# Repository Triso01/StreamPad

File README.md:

The Case:

On the left the topplate and on the right the case.
You should print the TopPlate with 100% Gyroid infill.
The Case should be printed with 20%< Gyriod Infill.

The PCB:

The settings for the PCB should look like this: (You can change the color or surface finish!)

What is it made for?
I am a little streamer who needs a soundboard/"Streamdeck" and it is a good oportunity to get one "for free" :). 
I hope you all like the design (Its my first one in Fusion).

BOM:
HackPad Kit (You dont have a kit? You can find the components here: https://hackpad.hackclub.com/parts)
You also need 2x CD4051BM (these are Multiplexers)
!!The Case might change after I get the PCB!!

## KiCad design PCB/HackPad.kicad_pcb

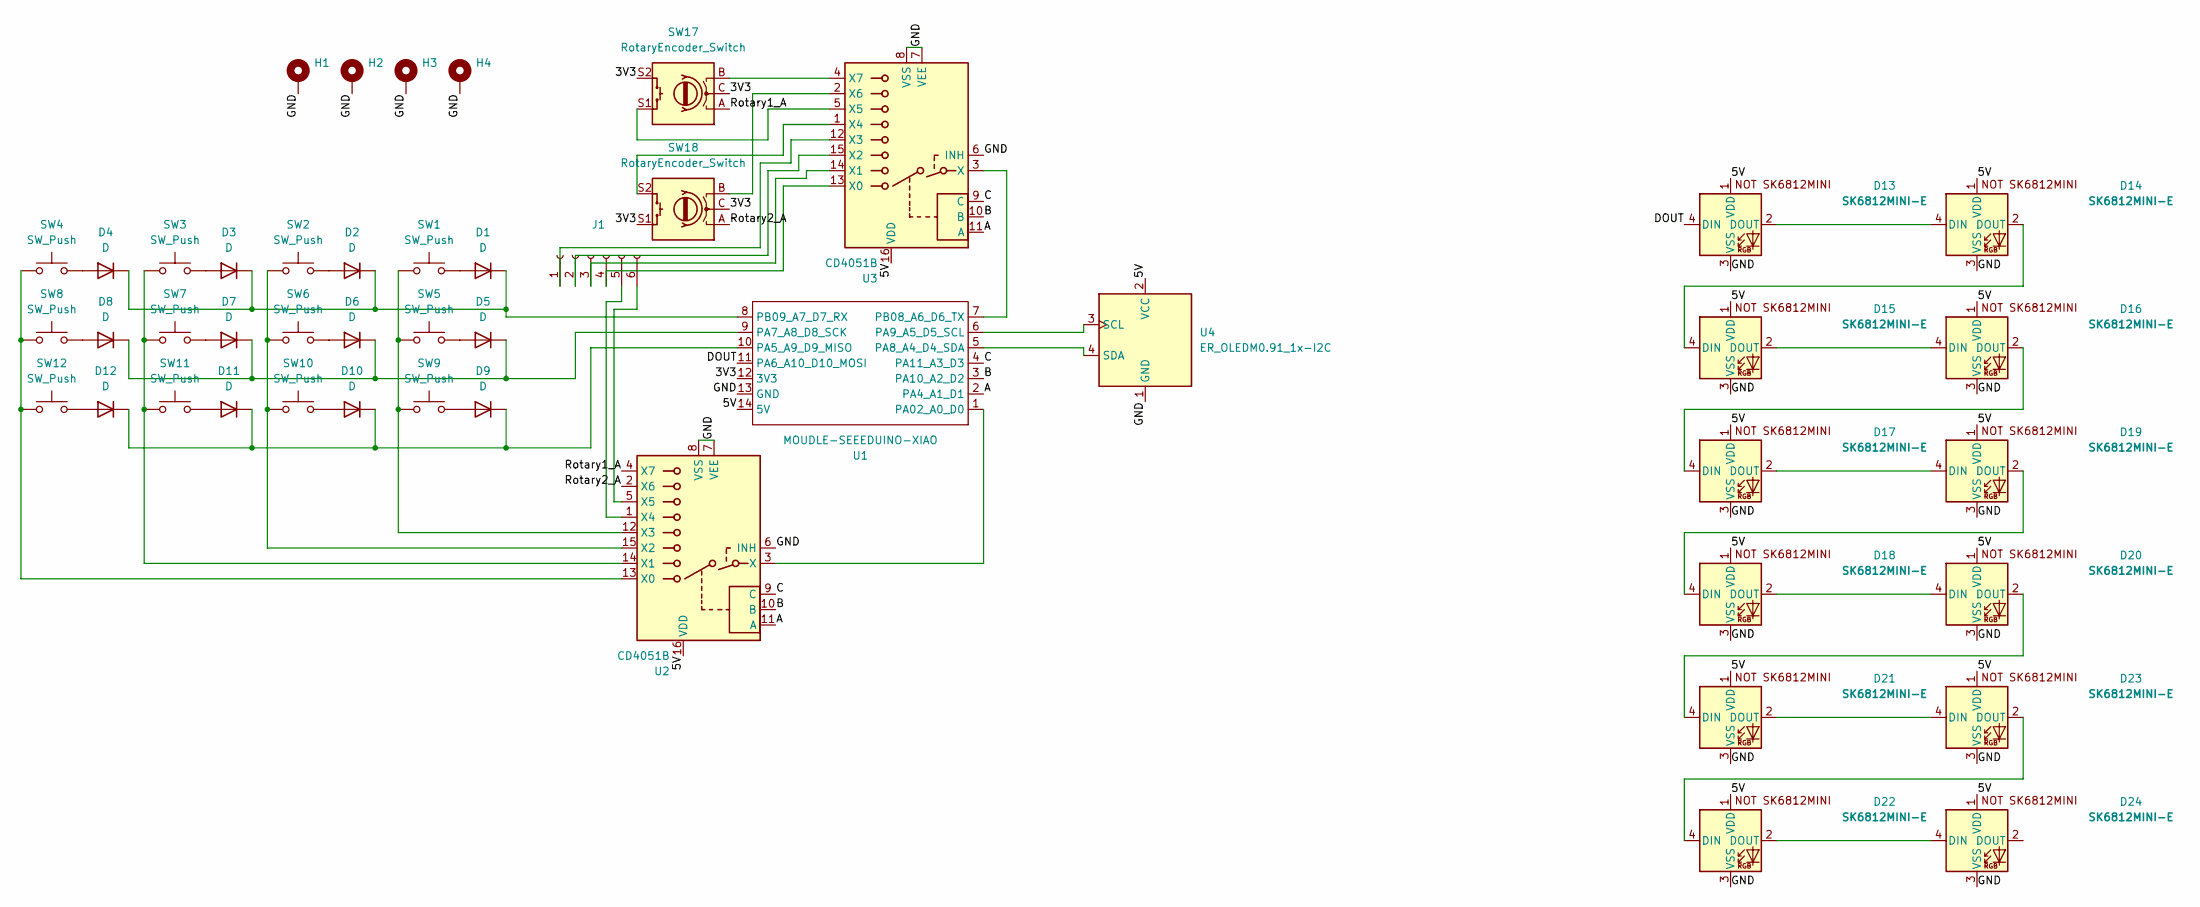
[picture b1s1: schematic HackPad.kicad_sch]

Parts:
D1, D2, D3, D4, D5, D6, D7, D8, D9, D10, D11, D12: D; D_DO-35_SOD27_P7.62mm_Horizontal
D13, D14, D15, D16, D17, D18, D19, D20, D21, D22, D23, D24: SK6812MINI-E; SK6812MINI-E_fixed
H1, H2, H3, H4: MountingHole_Pad; MountingHole_3.2mm_M3_DIN965_Pad
J1: Conn_01x06_Socket; PinSocket_1x06_P2.54mm_Vertical
SW1, SW2, SW3, SW4, SW5, SW6, SW7, SW8, SW9, SW10, SW11, SW12: SW_Push; SW_Cherry_MX_1.00u_PCB
SW17, SW18: RotaryEncoder_Switch; RotaryEncoder_Alps_EC11E-Switch_Vertical_H20mm_CircularMoun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
U1: MOUDLE-SEEEDUINO-XIAO; XIAO-Generic-Hybrid-14P-2.54-21X17.8MM
U2, U3: CD4051B; SOIC-16_3.9x9.9mm_P1.27mm
U4: ER_OLEDM0.91_1x-I2C

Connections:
/3V3: SW17.C, SW17.S2, SW18.C, SW18.S1, U1.12 (3V3)
/5V: D13.1 (VDD), D14.1 (VDD), D15.1 (VDD), D16.1 (VDD), D17.1 (VDD), D18.1 (VDD), D19.1 (VDD), D20.1 (VDD), D21.1 (VDD), D22.1 (VDD), D23.1 (VDD), D24.1 (VDD), U1.14 (5V), U2.16 (VDD), U3.16 (VDD), U4.2 (VCC)
/A: U1.2 (PA4_A1_D1), U2.11 (A), U3.11 (A)
/B: U1.3 (PA10_A2_D2), U2.10 (B), U3.10 (B)
/C: U1.4 (PA11_A3_D3), U2.9 (C), U3.9 (C)
/DOUT: D13.4 (DIN), U1.11 (PA6_A10_D10_MOSI)
/GND: D13.3 (VSS), D14.3 (VSS), D15.3 (VSS), D16.3 (VSS), D17.3 (VSS), D18.3 (VSS), D19.3 (VSS), D20.3 (VSS), D21.3 (VSS), D22.3 (VSS), D23.3 (VSS), D24.3 (VSS), H1.1 (1_1), H2.1 (1_1), H3.1 (1_1), H4.1 (1_1), U1.13 (GND), U2.6 (INH), U2.7 (VEE), U2.8 (VSS), U3.6 (INH), U3.7 (VEE), U3.8 (VSS), U4.1 (GND)
/Rotary1_A: SW17.A, U2.4 (X7)
/Rotary2_A: SW18.A, U2.2 (X6)
unnamed: D1.2 (A), SW1.1
unnamed: D1.1 (K), D2.1 (K), D3.1 (K), D4.1 (K), U1.8 (PB09_A7_D7_RX)
unnamed: D2.2 (A), SW2.1
unnamed: D3.2 (A), SW3.1
unnamed: D4.2 (A), SW4.1
unnamed: D5.2 (A), SW5.1
unnamed: D5.1 (K), D6.1 (K), D7.1 (K), D8.1 (K), U1.9 (PA7_A8_D8_SCK)
unnamed: D6.2 (A), SW6.1
unnamed: D7.2 (A), SW7.1
unnamed: D8.2 (A), SW8.1
unnamed: D9.2 (A), SW9.1
unnamed: D10.2 (A), SW10.1
unnamed: D9.1 (K), D10.1 (K), D11.1 (K), D12.1 (K), U1.10 (PA5_A9_D9_MISO)
unnamed: D11.2 (A), SW11.1
unnamed: D12.2 (A), SW12.1
unnamed: D13.2 (DOUT), D14.4 (DIN)
unnamed: D14.2 (DOUT), D15.4 (DIN)
unnamed: D15.2 (DOUT), D16.4 (DIN)
unnamed: D16.2 (DOUT), D17.4 (DIN)
unnamed: D17.2 (DOUT), D19.4 (DIN)
unnamed: D18.4 (DIN), D19.2 (DOUT)
unnamed: D18.2 (DOUT), D20.4 (DIN)
unnamed: D20.2 (DOUT), D21.4 (DIN)
unnamed: D21.2 (DOUT), D23.4 (DIN)
unnamed: D22.4 (DIN), D23.2 (DOUT)
unnamed: D22.2 (DOUT), D24.4 (DIN)
unnamed: J1.1, U3.12 (X3)
unnamed: J1.2, U3.15 (X2)
unnamed: J1.3, U3.14 (X1)
unnamed: J1.4, U3.13 (X0)
unnamed: J1.5, U2.1 (X4)
unnamed: J1.6, U2.5 (X5)
unnamed: U1.1 (PA02_A0_D0), U2.3 (X)
unnamed: U1.5 (PA8_A4_D4_SDA), U4.4 (SDA)
unnamed: U1.6 (PA9_A5_D5_SCL), U4.3 (SCL)
unnamed: U1.7 (PB08_A6_D6_TX), U3.3 (X)
unnamed: SW4.2, SW8.2, SW12.2, U2.13 (X0)
unnamed: SW3.2, SW7.2, SW11.2, U2.14 (X1)
unnamed: SW2.2, SW6.2, SW10.2, U2.15 (X2)
unnamed: SW1.2, SW5.2, SW9.2, U2.12 (X3)
unnamed: SW18.S2, U3.1 (X4)
unnamed: SW17.S1, U3.5 (X5)
unnamed: SW18.B, U3.2 (X6)
unnamed: SW17.B, U3.4 (X7)

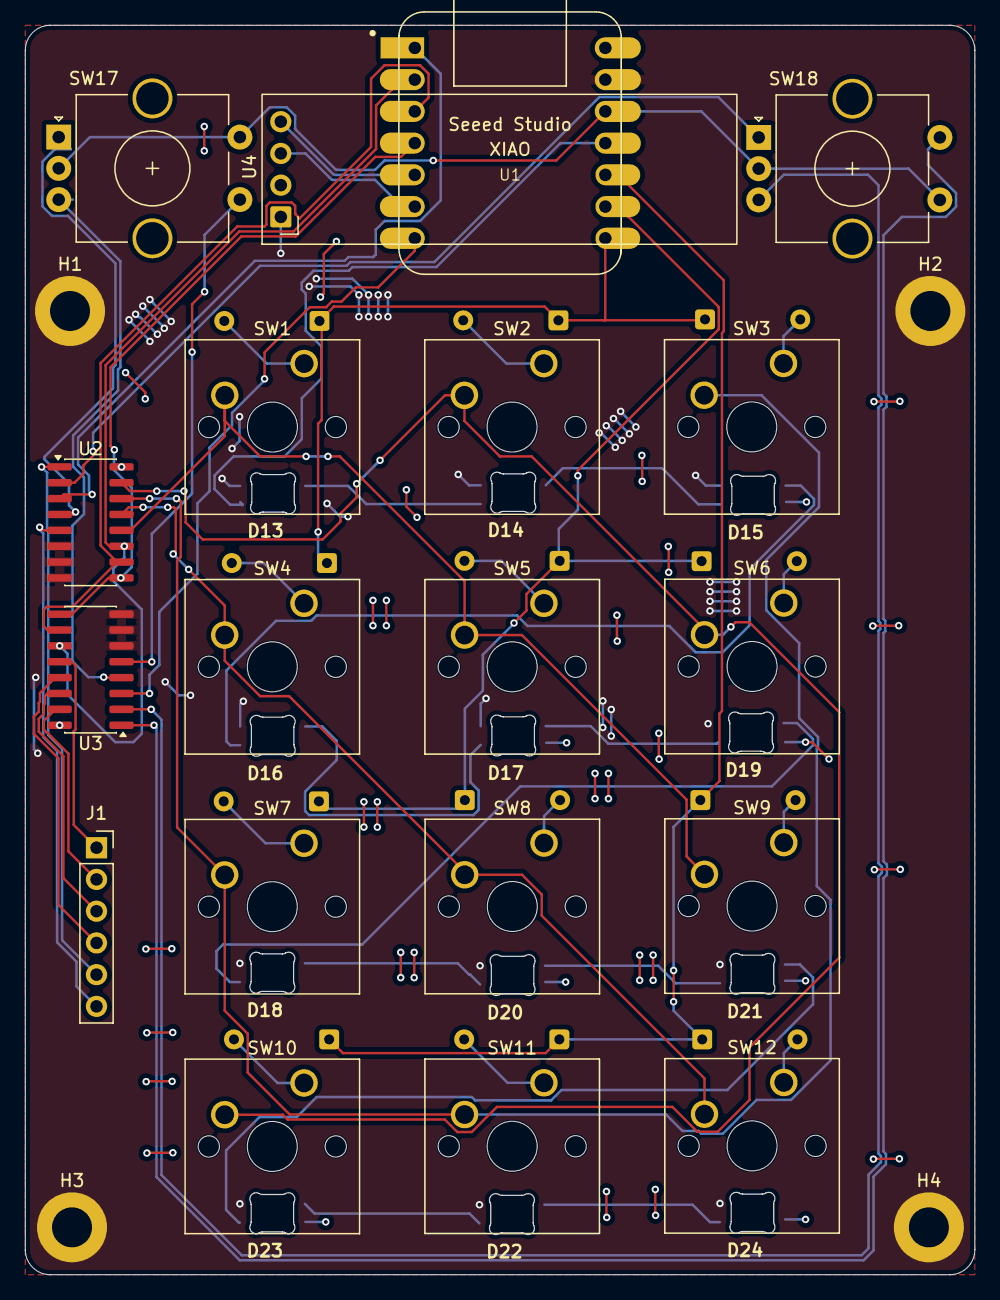
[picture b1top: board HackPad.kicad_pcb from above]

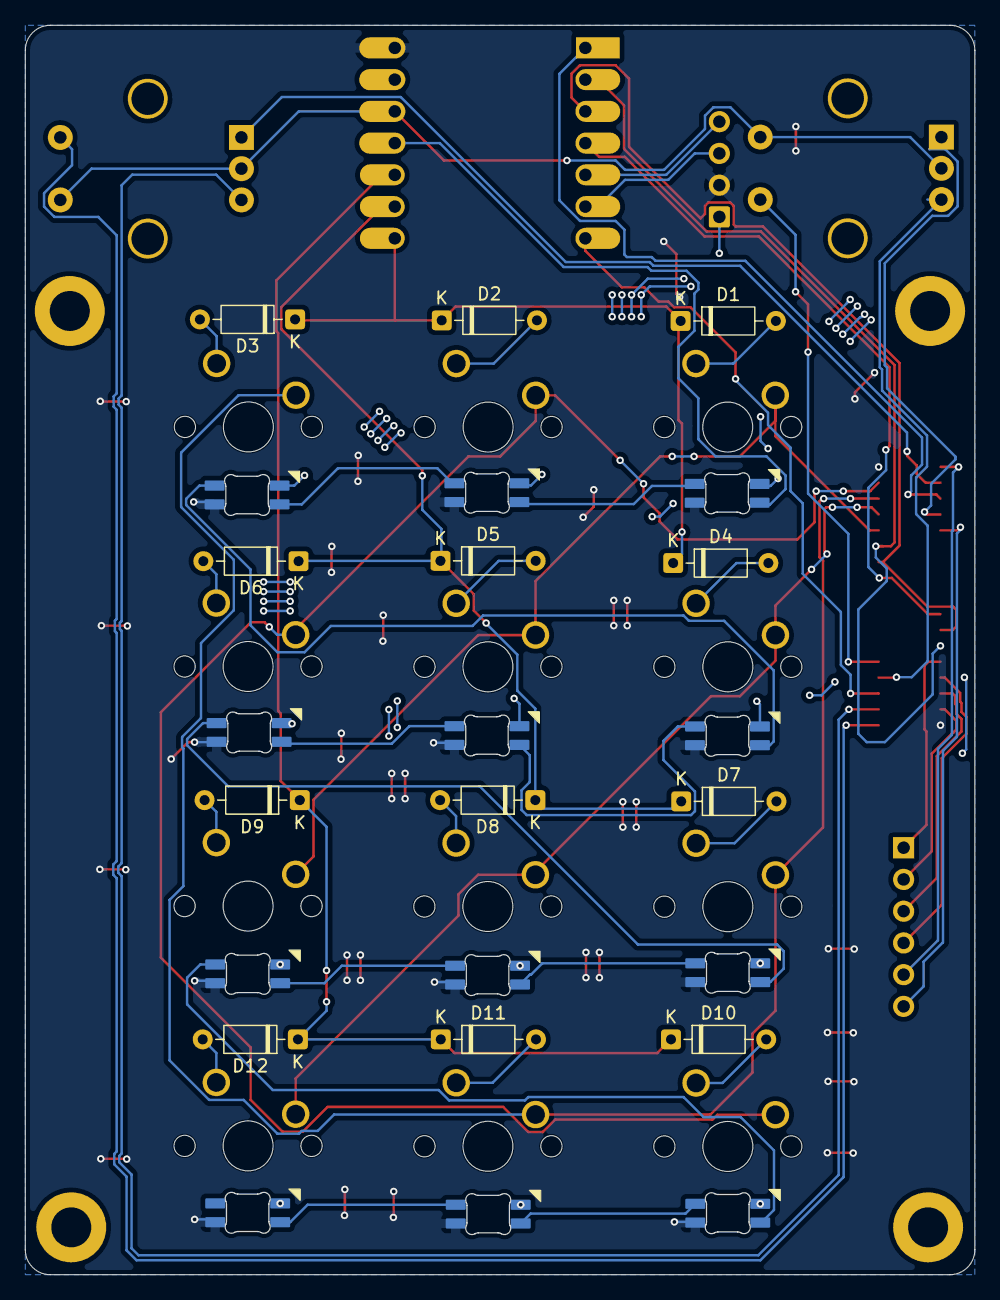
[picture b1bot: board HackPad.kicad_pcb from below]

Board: 2 copper layers, 76.0 x 100.0 mm, 47 parts (12 on the bottom side), 53 nets.
